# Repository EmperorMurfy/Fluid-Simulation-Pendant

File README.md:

# Fluid Simulation Pendant
A Fluid Simulation Pendant Inspired by Mitxela

<table>
  <tr>
    <td></td>
    <td></td>
  </tr>
</table>

## Overview
Since January, I've been particularly inspired by Mitxela's Fluid Simulation Pendant.
A watch-sized device, it contains it's own charlieplexed LED display driven by an STM32.
This allows the device to run a particle simulation that responds to gravity in real time.
In other words, water is displayed on it's LED display that flows and settles naturally as you move.
 
As a beginner, I was thoroughly intrigued. This came at the perfect opportunity as I sought to enter electronic design.
So, with no former experience, I set out to build my own from scratch.

You can find my full devlog at [Blueprint](https://blueprint.hackclub.com/projects/14158)
--

## PCB
This project was designed in KiCAD. V1 utilized a lilypad design with two 2-layer daughter boards (see devlog).
V2 features a singular 4-layer board, merging V1's two daughter boards. It tackles significant issues from V1.

### Schematic

### PCB
<table>
  <tr>
    <td></td>
    <td></td>
  </tr>
</table>

## 3D View

<table>
  <tr>
    <td></td>
    <td></td>
  </tr>
</table>

## Setup

OBTAIN PCB
1) Download project files from Github. Use KiCAD to open hardware files.
2) Export & Upload to JLCPCB through Fabrication Toolkit
3) Select PCBA. Make sure you click on Standard + assemble on both sides. 
4) Follow on screen instructions. Verify BOM contents.

5) Purchase and await arrival.

While waiting, you can 3D print the case included in the CAD folder.
Download both "Case.3mf" and "Back Lid.3mf"
Alternatively, you can access the CAD on [Onshape](https://cad.onshape.com/documents/ce3587694f856aec528b28ab/w/4bfd7fa16d33233767ff6bdf/e/73e8d055661068f7b677968e?renderMode=0&uiState=69cc9a998e56fd57fc1aa12d)

ASSEMBLY 
1) Solder PH1 pins on the back of the PCB at drilled holes labeled BOOT0, NRST, DEBUG_TMS, GND, DEBUG_TCK, 3.3V
2) Connect to Nucleo's ST-LINK, Connect to PCB
3) Install STM32CubeProgrammer and STM32CubeIDE
4) Open software folder from downloaded project files, select STM32.ioc (this should open STM32CubeProgrammer)
5) Select generate code (this should open STM32CubeIDE)
6) Replace the generated main.cp or cpp with main.cp from project files, click run to save
8) Install PCB to case - Be CAREFUL! Putting it at an angle with the USB-C pointed towards the opening helps.
9) Plug the battery into PCB's JST-2 port
10) Install the back lid + push in the watch glass

## BOM
In order to program this device, you will need F to F Jumper Wire and a Nucleo (I used Nucleo-F446RE). 
I didn't include these items as you may already have them. Disclaimer: The cost and quantity of PCB components were determined by JLCPCB.
JLCPCB sources their components from LCSC, but price may be inaccurate. Likewise, JLCPCB charged more components than required (e.g I only need 1040 Green 0402 LEDs, not 1045)
Likewise, you'll need to order 5 PCBs & 2 PCBA minimum. I ordered 5 PCBs + associated PCBA. 

|Item                         |Qty |Cost  |URL                                                                                                                                                                                                                                                 |Reference                                                                                                                                                                                                                                                                                                                                                                                                                                                                                                                                                                                                                                                                                                                                                                                                                                                                                                                                                                                       |Mfg Part #            |
|-----------------------------|----|------|----------------------------------------------------------------------------------------------------------------------------------------------------------------------------------------------------------------------------------------------------|------------------------------------------------------------------------------------------------------------------------------------------------------------------------------------------------------------------------------------------------------------------------------------------------------------------------------------------------------------------------------------------------------------------------------------------------------------------------------------------------------------------------------------------------------------------------------------------------------------------------------------------------------------------------------------------------------------------------------------------------------------------------------------------------------------------------------------------------------------------------------------------------------------------------------------------------------------------------------------------------|----------------------|
|PCB                          |5   |$14.90|https://jlcpcb.com/                                                                                                                                                                                                                                 |-                                                                                                                                                                                                                                                                                                                                                                                                                                                                                                                                                                                                                                                                                                                                                                                                                                                                                                                                                                                               |-                     |
|4.7uF-0402                   |20  |$0.11 |https://www.lcsc.com/product-detail/C23733.html                                                                                                                                                                                                     |C1,C8                                                                                                                                                                                                                                                                                                                                                                                                                                                                                                                                                                                                                                                                                                                                                                                                                                                                                                                                                                                           |CL05A475MP5NRNC       |
|100nF-0402                   |40  |$0.05 |https://www.lcsc.com/product-detail/C1525.html?s_z=n_CL05B104KO5NNNC&spm=wm.ssy.bg.0.xh&lcsc_vid=EwBZBVRfFVVaVFdSR1hcUFBTQFUMUl1eEVFaVldeEQIxVlNRQlFeUVBfQFJcVzsOAxUeFF5JWBYZEEoKFBINSQcJGk4eFQsCAgIaSgADAwAHC0slRVJZVFdIHxUDCw%3D%3D               |C2,C3,C4,C5,C6,C7                                                                                                                                                                                                                                                                                                                                                                                                                                                                                                                                                                                                                                                                                                                                                                                                                                                                                                                                                                               |CL05B104KO5NNNC       |
|1uF                          |30  |$0.12 |https://www.lcsc.com/product-detail/C52923.html?s_z=n_CL05A105KA5NQNC&spm=wm.ssy.bg.0.xh&lcsc_vid=EwBZBVRfFVVaVFdSR1hcUFBTQFUMUl1eEVFaVldeEQIxVlNRQlFeUVFTQ1heXzsOAxUeFF5JWBYZEEoKFBINSQcJGk4eFQsCAgIaSgADAwAHC0slRlRcUkoOAwwC                      |C9,C10                                                                                                                                                                                                                                                                                                                                                                                                                                                                                                                                                                                                                                                                                                                                                                                                                                                                                                                                                                                          |CL05A105KA5NQNC       |
|1uF-0402                     |-   |-     |https://www.lcsc.com/product-detail/C52923.html?s_z=n_CL05A105KA5NQNC&spm=wm.ssy.bg.0.xh&lcsc_vid=EwBZBVRfFVVaVFdSR1hcUFBTQFUMUl1eEVFaVldeEQIxVlNRQlFeUVFTQ1heXzsOAxUeFF5JWBYZEEoKFBINSQcJGk4eFQsCAgIaSgADAwAHC0slRlRcUkoOAwwC                      |C11,C12                                                                                                                                                                                                                                                                                                                                                                                                                                                                                                                                                                                                                                                                                                                                                                                                                                                                                                                                                                                         |CL05A105KA5NQNC       |
|Green 0402 LED               |1045|$29.88|https://www.lcsc.com/product-detail/C74338.html?s_z=n_16-213%252FGHC-YR1S1%252F3T&spm=wm.ssy.bg.0.xh&lcsc_vid=EwBZBVRfFVVaVFdSR1hcUFBTQFUMUl1eEVFaVldeEQIxVlNRQlFeUVNQQlJfVDsOAxUeFF5JWBYZEEoKFBINSQcJGk4eFQsCAgIaSgADAwAHC0slRVdaU1RRWQkaCgg%3D    |D6,D7,D8,D9,D10,D11,D20,D21,D22,D23,D24,D25,D26,D27,D28,D29,D35,D36,D37,D38,D39,D40,D41,D42,D43,D44,D45,D46,D50,D51,D52,D53,D54,D55,D56,D57,D58,D59,D60,D61,D62,D63,D66,D67,D68,D69,D70,D71,D72,D73,D74,D75,D76,D77,D78,D79,D81,D82,D83,D84,D85,D86,D87,D88,D89,D90,D91,D92,D93,D94,D95,D96,D97,D98,D99,D100,D101,D102,D103,D104,D105,D106,D107,D108,D109,D110,D111,D112,D113,D114,D115,D116,D117,D118,D119,D120,D121,D122,D123,D124,D125,D126,D127,D128,D129,D130,D131,D132,D133,D134,D135,D136,D137,D138,D139,D140,D141,D142,D143,D144,D145,D146,D147,D148,D149,D150,D151,D152,D153,D154,D155,D156,D157,D158,D159,D160,D161,D162,D163,D164,D165,D166,D167,D168,D169,D170,D171,D172,D173,D174,D175,D176,D178,D179,D180,D181,D182,D183,D184,D185,D186,D187,D188,D189,D190,D191,D194,D195,D196,D197,D198,D199,D200,D201,D202,D203,D204,D205,D206,D207,D211,D212,D213,D214,D215,D216,D217,D218,D219,D220,D221,D222,D228,D229,D230,D231,D232,D233,D234,D235,D236,D237,D246,D247,D248,D249,D250,D251|16-213/GHC-YR1S1/3T   |
|Red 0402 LED                 |5   |$0.35 |https://www.lcsc.com/product-detail/C264407.html?s_z=n_16-213%252FR6C-AQ2R2B%252F3T&spm=wm.ssy.bg.0.xh&lcsc_vid=EwBZBVRfFVVaVFdSR1hcUFBTQFUMUl1eEVFaVldeEQIxVlNRQlFeUVFRR1RZUzsOAxUeFF5JWBYZEEoKFBINSQcJGk4eFQsCAgIaSgADAwAHC0slQlNXVVdIHxUDCw%3D%3D|D257                                                                                                                                                                                                                                                                                                                                                                                                                                                                                                                                                                                                                                                                                                                                                                                                                                                                                                                                                                                            |16-213/R6C-AQ2R2B/3T  |
|Conn_01x01_Pin               |125 |-     |-                                                                                                                                                                                                                                                   |J2,J3,J4,J5,J6,J7,J8,J9,J10,J11,J12,J13,J14,J15,J16,J17,J18,J19,J20,J21,J22,J23,J24,J25,J26                                                                                                                                                                                                                                                                                                                                                                                                                                                                                                                                                                                                                                                                                                                                                                                                                                                                                                     |DNP                   |
|Conn_01x02_Socket            |5   |$2.19 |https://www.lcsc.com/product-detail/C160352.html?s_z=n_C160352                                                                                                                                                                                      |J44                                                                                                                                                                                                                                                                                                                                                                                                                                                                                                                                                                                                                                                                                                                                                                                                                                                                                                                                                                                             |B2B-PH-SM4-TB(LF)(SN) |
|22                           |95  |$0.08 |https://www.lcsc.com/product-detail/C25092.html?s_z=n_0402WGF220JTCE&spm=wm.ssy.bg.0.xh&lcsc_vid=EwBZBVRfFVVaVFdSR1hcUFBTQFUMUl1eEVFaVldeEQIxVlNRQlFeUVxUTlhbUzsOAxUeFF5JWBYZEEoKFBINSQcJGk4eFQsCAgIaSgADAwAHC0slRldeVFFUWQkaCgg%3D                 |R1,R2,R3,R4,R5,R6,R7,R8,R9,R10,R11,R12,R13,R14,R15,R16,R17                                                                                                                                                                                                                                                                                                                                                                                                                                                                                                                                                                                                                                                                                                                                                                                                                                                                                                                                      |0402WGF220JTCE        |
|20K                          |20  |$0.02 |https://www.lcsc.com/product-detail/C25765.html?s_z=n_0402WGF2002TCE&spm=wm.ssy.bg.0.xh&lcsc_vid=EwBZBVRfFVVaVFdSR1hcUFBTQFUMUl1eEVFaVldeEQIxVlNRQlFeUVxSRlRXVTsOAxUeFF5JWBYZEEoKFBINSQcJGk4eFQsCAgIaSgADAwAHC0slRVReXlZIHxUDCw%3D%3D               |R18                                                                                                                                                                                                                                                                                                                                                                                                                                                                                                                                                                                                                                                                                                                                                                                                                                                                                                                                                                                             |0402WGF2002TCE        |
|1k                           |20  |$0.01 |https://www.lcsc.com/product-detail/C11702.html?s_z=n_0402WGF1001TC&spm=wm.ssy.bg.0.xh&lcsc_vid=Q1MNU1YDQwJcBgIAEldWVQcERldfAVZWEQRaBlNWQVQxVlNRQlFfVVZTR1RcXjsOAxUeFF5JWBYZEEoKFBINSQcJGk4eFQsCAgIaSgADAwAHC0slRVRZUVFIHxUDCw%3D%3D                |R19                                                                                                                                                                                                                                                                                                                                                                                                                                                                                                                                                                                                                                                                                                                                                                                                                                                                                                                                                                                             |0402WGF1001TC         |
|10k                          |25  |$0.03 |https://www.lcsc.com/product-detail/C25744.html?s_z=n_0402WGF1002TCE&spm=wm.ssy.bg.0.xh&lcsc_vid=EwBZBVRfFVVaVFdSR1hcUFBTQFUMUl1eEVFaVldeEQIxVlNRQlFeUVxQQ1BdUDsOAxUeFF5JWBYZEEoKFBINSQcJGk4eFQsCAgIaSgADAwAHC0slRlBZV1ZIHxUDCw%3D%3D               |R20, R21,R22                                                                                                                                                                                                                                                                                                                                                                                                                                                                                                                                                                                                                                                                                                                                                                                                                                                                                                                                                                                    |0402WGF1002TCE        |
|5.1K                         |20  |$0.02 |https://www.lcsc.com/product-detail/C25905.html?s_z=n_0402WGF5101TCE&spm=wm.ssy.bg.0.xh&lcsc_vid=EwBZBVRfFVVaVFdSR1hcUFBTQFUMUl1eEVFaVldeEQIxVlNRQlFeUVxRR1dXUjsOAxUeFF5JWBYZEEoKFBINSQcJGk4eFQsCAgIaSgADAwAHC0slRVRZU1BIHxUDCw%3D%3D               |R23,R24                                                                                                                                                                                                                                                                                                                                                                                                                                                                                                                                                                                                                                                                                                                                                                                                                                                                                                                                                                                         |0402WGF5101TCE        |
|TestPoint                    |15  |      |-                                                                                                                                                                                                                                                   |TP1,TP2,TP3                                                                                                                                                                                                                                                                                                                                                                                                                                                                                                                                                                                                                                                                                                                                                                                                                                                                                                                                                                                     |DNP                   |
|STM32U575RGTx                |5   |$27.84|                                                                                                                                                                                                                                                    |U1                                                                                                                                                                                                                                                                                                                                                                                                                                                                                                                                                                                                                                                                                                                                                                                                                                                                                                                                                                                              |STM32U575RGT6         |
|ADXL363                      |5   |$90.77|https://www.lcsc.com/product-detail/C579464.html?s_z=n_ADXL363&spm=wm.ssy.bg.2.xh&lcsc_vid=EwBZBVRfFVVaVFdSR1hcUFBTQFUMUl1eEVFaVldeEQIxVlNRQlFeUV1WT1ReVzsOAxUeFF5JWBYZEEoKFBINSQcJGk4eFQsCAgIaSgADAwAHC0slRVRXV1FIHxUDCw%3D%3D                     |U2                                                                                                                                                                                                                                                                                                                                                                                                                                                                                                                                                                                                                                                                                                                                                                                                                                                                                                                                                                                              |ADXL363BCCZ-RL7       |
|USBLC6-2P6                   |5   |$1.23 |https://www.lcsc.com/product-detail/C15999.html?s_z=n_USBLC6-2P6&spm=wm.ssy.bg.0.xh&lcsc_vid=EwBZBVRfFVVaVFdSR1hcUFBTQFUMUl1eEVFaVldeEQIxVlNRQlFeUV1SRVdZUzsOAxUeFF5JWBYZEEoKFBINSQcJGk4eFQsCAgIaSgADAwAHC0slQlZXU1JSWQkaCgg%3D                     |U3                                                                                                                                                                                                                                                                                                                                                                                                                                                                                                                                                                                                                                                                                                                                                                                                                                                                                                                                                                                              |USBLC6-2P6            |
|MCP73832-2-MC                |5   |$5.19 |https://www.lcsc.com/product-detail/C511264.html?s_z=n_MCP73832T-2ACI%252FMC&spm=wm.ssy.bg.0.xh&lcsc_vid=EwBZBVRfFVVaVFdSR1hcUFBTQFUMUl1eEVFaVldeEQIxVlNRQlFeUV1TTlVfVjsOAxUeFF5JWBYZEEoKFBINSQcJGk4eFQsCAgIaSgADAwAHC0slRlRXXl1IHxUDCw%3D%3D       |U4                                                                                                                                                                                                                                                                                                                                                                                                                                                                                                                                                                                                                                                                                                                                                                                                                                                                                                                                                                                              |MCP73832T-2ACI/MC     |
|TPS7A20xxxDQN                |5   |$1.59 |https://www.lcsc.com/product-detail/C46459900.html?s_z=n_TPS7A2033DQNR&spm=wm.ssy.bg.0.xh&lcsc_vid=EwBZBVRfFVVaVFdSR1hcUFBTQFUMUl1eEVFaVldeEQIxVlNRQlFeUV1QT1NbXjsOAxUeFF5JWBYZEEoKFBINSQcJGk4eFQsCAgIaSgADAwAHC0slQlBfVVJSWQkaCgg%3D               |U5                                                                                                                                                                                                                                                                                                                                                                                                                                                                                                                                                                                                                                                                                                                                                                                                                                                                                                                                                                                              |TPS7A2033DQNR         |
|TYPE-C_16P_QTWT              |5   |$0.45 |https://www.lcsc.com/product-detail/C5187472.html?s_z=n_TYPE-C%252016P%2520QTWT&spm=wm.ssy.bg.0.xh&lcsc_vid=EwBZBVRfFVVaVFdSR1hcUFBTQFUMUl1eEVFaVldeEQIxVlNRQlFeUV1RQVdfVjsOAxUeFF5JWBYZEEoKFBINSQcJGk4eFQsCAgIaSgADAwAHC0slQ1daUl1fR1FADxALGw%3D%3D|USB1                                                                                                                                                                                                                                                                                                                                                                                                                                                                                                                                                                                                                                                                                                                                                                                                                                                                                                                                                                                            |TYPE-C 16P QTWT       |
|Setup Fee                    |-   |$50.74|-                                                                                                                                                                                                                                                   |-                                                                                                                                                                                                                                                                                                                                                                                                                                                                                                                                                                                                                                                                                                                                                                                                                                                                                                                                                                                               |-                     |
|Stencil                      |-   |$16.30|-                                                                                                                                                                                                                                                   |-                                                                                                                                                                                                                                                                                                                                                                                                                                                                                                                                                                                                                                                                                                                                                                                                                                                                                                                                                                                               |-                     |
|Feeders Loading Fee          |-   |$25.84|-                                                                                                                                                                                                                                                   |-                                                                                                                                                                                                                                                                                                                                                                                                                                                                                                                                                                                                                                                                                                                                                                                                                                                                                                                                                                                               |-                     |
|SMT Assembly                 |-   |$5.23 |-                                                                                                                                                                                                                                                   |-                                                                                                                                                                                                                                                                                                                                                                                                                                                                                                                                                                                                                                                                                                                                                                                                                                                                                                                                                                                               |-                     |
|Packaging Fee                |    |$0.49 |-                                                                                                                                                                                                                                                   |-                                                                                                                                                                                                                                                                                                                                                                                                                                                                                                                                                                                                                                                                                                                                                                                                                                                                                                                                                                                               |-                     |
|JLCPCB Shipping              |-   |$50.04|-                                                                                                                                                                                                                                                   |-                                                                                                                                                                                                                                                                                                                                                                                                                                                                                                                                                                                                                                                                                                                                                                                                                                                                                                                                                                                               |-                     |
|JLCPCB Custom Duties & Taxes |-   |$86.68|-                                                                                                                                                                                                                                                   |-                                                                                                                                                                                                                                                                                                                                                                                                                                                                                                                                                                                                                                                                                                                                                                                                                                                                                                                                                                                               |-                     |
|Li-Polymer 402025 150mAh 3.7V|5   |$29.75|https://www.digikey.com/en/products/detail/adafruit-industries-llc/1317/5054547                                                                                                                                                                     |-                                                                                                                                                                                                                                                                                                                                                                                                                                                                                                                                                                                                                                                                                                                                                                                                                                                                                                                                                                                               |-                     |
|PH1-01-UA                    |40  |$1.16 |https://www.digikey.com/en/products/detail/adam-tech/PH1-01-UA/9830231                                                                                                                                                                              |-                                                                                                                                                                                                                                                                                                                                                                                                                                                                                                                                                                                                                                                                                                                                                                                                                                                                                                                                                                                               |-                     |
|Digikey Shipping             |-   |$6.99 |-                                                                                                                                                                                                                                                   |-                                                                                                                                                                                                                                                                                                                                                                                                                                                                                                                                                                                                                                                                                                                                                                                                                                                                                                                                                                                               |-                     |
|Watch Glass 43mm Dia         |1   |$7.69 |https://www.amazon.com/dp/B09QXCGNG6?ref_=ppx_hzsearch_conn_dt_b_fed_asin_title_1                                                                                                                                                                   |                                                                                                                                                                                                                                                                                                                                                                                                                                                                                                                                                                                                                                                                                                                                                                                                                                                                                                                                                                                                |                      |
|Total                        |-   |$456  |                                                                                                                                                                                                                                                    |                                                                                                                                                                                                                                                                                                                                                                                                                                                                                                                                                                                                                                                                                                                                                                                                                                                                                                                                                                                                |                      |

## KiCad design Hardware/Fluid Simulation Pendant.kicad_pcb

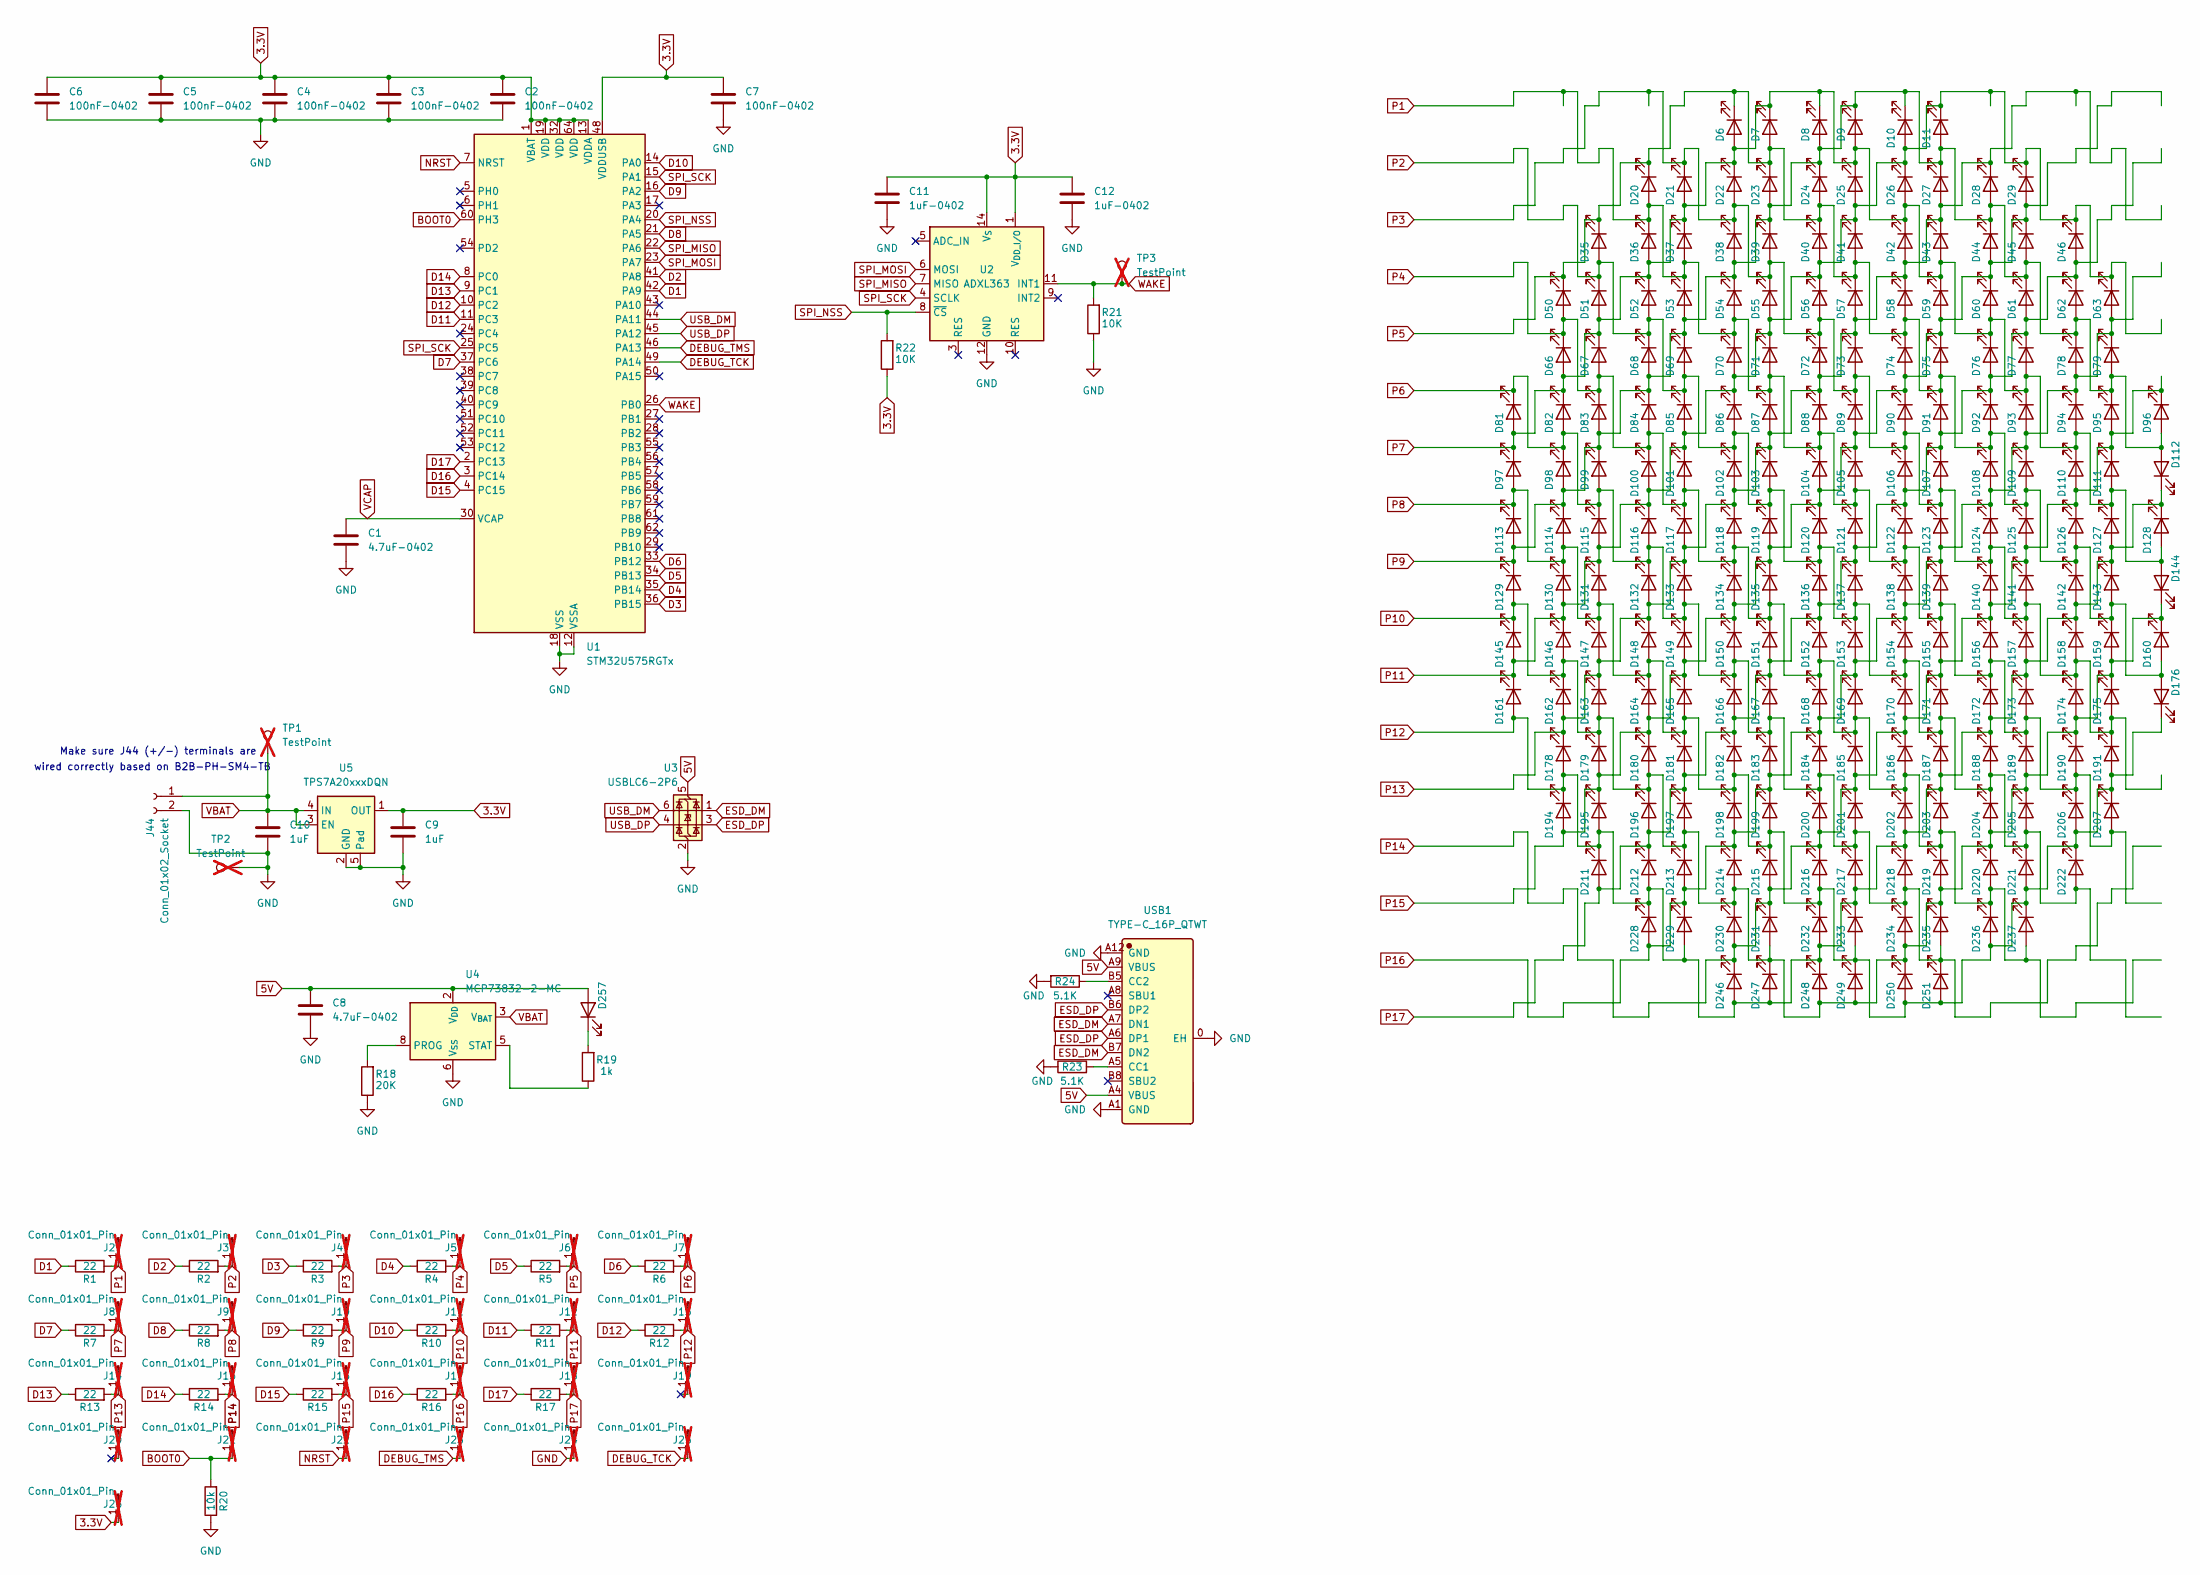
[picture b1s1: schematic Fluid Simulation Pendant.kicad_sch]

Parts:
C1, C8: 4.7uF-0402; C_0402_1005Metric; Mfg Part # CL05A475MP5NRNC
C2, C3, C4, C5, C6, C7: 100nF-0402; C_0402_1005Metric; Mfg Part # CL05B104KO5NNNC
C9, C10: 1uF; C_0402_1005Metric; Mfg Part # CL05A105KA5NQNC
C11, C12: 1uF-0402; C_0402_1005Metric; Mfg Part # CL05A105KA5NQNC
D6, D7, D8, D9, D10, D11, D20, D21, D22, D23, D24, D25, D26, D27, D28, D29, D35, D36, D37, D38, D39, D40, D41, D42, D43, D44, D45, D46, D50, D51, D52, D53, D54, D55, D56, D57, D58, D59, D60, D61, D62, D63, D66, D67, D68, D69, D70, D71, D72, D73, D74, D75, D76, D77, D78, D79, D81, D82, D83, D84, D85, D86, D87, D88, D89, D90, D91, D92, D93, D94, D95, D96, D97, D98, D99, D100, D101, D102, D103, D104, D105, D106, D107, D108, D109, D110, D111, D112, D113, D114, D115, D116, D117, D118, D119, D120, D121, D122, D123, D124, D125, D126, D127, D128, D129, D130, D131, D132, D133, D134, D135, D136, D137, D138, D139, D140, D141, D142, D143, D144, D145, D146, D147, D148, D149, D150, D151, D152, D153, D154, D155, D156, D157, D158, D159, D160, D161, D162, D163, D164, D165, D166, D167, D168, D169, D170, D171, D172, D173, D174, D175, D176, D178, D179, D180, D181, D182, D183, D184, D185, D186, D187, D188, D189, D190, D191, D194, D195, D196, D197, D198, D199, D200, D201, D202, D203, D204, D205, D206, D207, D211, D212, D213, D214, D215, D216, D217, D218, D219, D220, D221, D222, D228, D229, D230, D231, D232, D233, D234, D235, D236, D237, D246, D247, D248, D249, D250, D251: Green 0402 LED; LED_0402_1005Metric; Mfg Part # 16-213/GHC-YR1S1/3T
D257: Red 0402 LED; LED_0402_1005Metric; Mfg Part # 16-213/R6C-AQ2R2B/3T
J2, J3, J4, J5, J6, J7, J8, J9, J10, J11, J12, J13, J14, J15, J16, J17, J18, J19, J20, J21, J22, J23, J24, J25, J26: Conn_01x01_Pin; TestPoint_THTPad_D2.0mm_Drill1.0mm; not fitted
J44: Conn_01x02_Socket; JST_PH_B2B-PH-SM4-TB_1x02-1MP_P2.00mm_Vertical; Mfg Part # B2B-PH-SM4-TB(LF)(SN)
R1, R2, R3, R4, R5, R6, R7, R8, R9, R10, R11, R12, R13, R14, R15, R16, R17: 22; R_0402_1005Metric; Mfg Part # 0402WGF220JTCE
R18: 20K; R_0402_1005Metric; Mfg Part # 0402WGF2002TCE
R19: 1k; R_0402_1005Metric; Mfg Part # 0402WGF1001TC
R20: 10k; R_0402_1005Metric; Mfg Part # 0402WGF1002TCE
R21, R22: 10K; R_0402_1005Metric; Mfg Part # 0402WGF1002TCE
R23, R24: 5.1K; R_0402_1005Metric; Mfg Part # 0402WGF5101TCE
TP1, TP2, TP3: TestPoint; TestPoint_Pad_2.0x2.0mm; not fitted
U1: STM32U575RGTx; LQFP-64_10x10mm_P0.5mm; Mfg Part # STM32U575RGT6
U2: ADXL363; Analog_LGA-16_3.25x3mm_P0.5mm_LayoutBorder3x5y; Mfg Part # ADXL363BCCZ-RL7
U3: USBLC6-2P6; SOT-666; Mfg Part # USBLC6-2P6
U4: MCP73832-2-MC; DFN-8-1EP_3x2mm_P0.5mm_EP1.7x1.4mm; Mfg Part # MCP73832T-2ACI/MC
U5: TPS7A20xxxDQN; Texas_X2SON-4_1x1mm_P0.65mm; Mfg Part # TPS7A2033DQNR
USB1: TYPE-C_16P_QTWT; Manufacturer Part TYPE-C 16P QTWT; LCSC C5187472

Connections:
3.3V: C2.1, C3.1, C4.1, C5.1, C6.1, C7.1, C9.1, C11.1, C12.1, J26.1, R22.1, U1.1 (VBAT), U1.13 (VDDA), U1.19 (VDD), U1.32 (VDD), U1.48 (VDDUSB), U1.64 (VDD), U2.1 (V_{DD_I/O}), U2.14 (V_{S}), U5.1 (OUT)
5V: C8.1, D257.2 (A), U3.5 (VBUS), U4.1 (V_{DD}), U4.2 (V_{DD}), USB1.A4 (VBUS), USB1.A9 (VBUS)
BOOT0: J21.1, R20.2, U1.60 (PH3)
D1: R1.1, U1.42 (PA9)
D2: R2.1, U1.41 (PA8)
D3: R3.1, U1.36 (PB15)
D4: R4.1, U1.35 (PB14)
D5: R5.1, U1.34 (PB13)
D6: R6.1, U1.33 (PB12)
D7: R7.1, U1.37 (PC6)
D8: R8.1, U1.21 (PA5)
D9: R9.1, U1.16 (PA2)
D10: R10.1, U1.14 (PA0)
D11: R11.1, U1.11 (PC3)
D12: R12.1, U1.10 (PC2)
D13: R13.1, U1.9 (PC1)
D14: R14.1, U1.8 (PC0)
D15: R15.1, U1.4 (PC15)
D16: R16.1, U1.3 (PC14)
D17: R17.1, U1.2 (PC13)
DEBUG_TCK: J25.1, U1.49 (PA14)
DEBUG_TMS: J23.1, U1.46 (PA13)
ESD_DM: U3.1 (I/O1), USB1.A7 (DN1), USB1.B7 (DN2)
ESD_DP: U3.3 (I/O2), USB1.A6 (DP1), USB1.B6 (DP2)
GND: C1.2, C2.2, C3.2, C4.2, C5.2, C6.2, C7.2, C8.2, C9.2, C10.2, C11.2, C12.2, J24.1, J44.2, R18.1, R20.1, R21.1, R23.1, R24.2, TP2.1, U1.12 (VSSA), U1.18 (VSS), U1.31 (VSS), U1.47 (VSS), U1.63 (VSS), U2.12 (GND), U2.13 (GND), U2.16 (GND), U3.2 (GND), U4.6 (V_{SS}), U5.2 (GND), U5.5 (Pad), USB1.0 (EH), USB1.A1 (GND), USB1.A12 (GND)
NRST: J22.1, U1.7 (NRST)
unnamed: D257.1 (K), R19.2
unnamed: R18.2, U4.8 (PROG)
unnamed: R19.1, U4.5 (STAT)
unnamed: R23.2, USB1.A5 (CC1)
unnamed: R24.1, USB1.B5 (CC2)
P1: D20.2 (A), D36.1 (K), D37.2 (A), D53.1 (K), D54.2 (A), D70.1 (K), D71.2 (A), D87.1 (K), D88.2 (A), D104.1 (K), D105.2 (A), D121.1 (K), D122.2 (A), D138.1 (K), D139.2 (A), D155.1 (K), D156.2 (A), D172.1 (K), D173.2 (A), D189.1 (K), D190.2 (A), D206.1 (K), D207.2 (A), J2.1, R1.2
P2: D35.2 (A), D51.1 (K), D52.2 (A), D68.1 (K), D69.2 (A), D85.1 (K), D86.2 (A), D102.1 (K), D103.2 (A), D119.1 (K), D120.2 (A), D136.1 (K), D137.2 (A), D153.1 (K), D154.2 (A), D170.1 (K), D171.2 (A), D187.1 (K), D188.2 (A), D204.1 (K), D205.2 (A), D221.1 (K), D222.2 (A), J3.1, R2.2
P3: D21.1 (K), D22.2 (A), D38.1 (K), D39.2 (A), D55.1 (K), D56.2 (A), D72.1 (K), D73.2 (A), D89.1 (K), D90.2 (A), D106.1 (K), D107.2 (A), D123.1 (K), D124.2 (A), D140.1 (K), D141.2 (A), D157.1 (K), D158.2 (A), D174.1 (K), D175.2 (A), D191.1 (K), J4.1, R3.2
P4: D50.2 (A), D66.1 (K), D67.2 (A), D83.1 (K), D84.2 (A), D100.1 (K), D101.2 (A), D117.1 (K), D118.2 (A), D134.1 (K), D135.2 (A), D151.1 (K), D152.2 (A), D168.1 (K), D169.2 (A), D185.1 (K), D186.2 (A), D202.1 (K), D203.2 (A), D219.1 (K), D220.2 (A), D236.1 (K), D237.2 (A), J5.1, R4.2
P5: D6.1 (K), D7.2 (A), D20.1 (K), D23.1 (K), D24.2 (A), D35.1 (K), D40.1 (K), D41.2 (A), D50.1 (K), D57.1 (K), D58.2 (A), D74.1 (K), D75.2 (A), D91.1 (K), D92.2 (A), D108.1 (K), D109.2 (A), D125.1 (K), D126.2 (A), D142.1 (K), D143.2 (A), D159.1 (K), D160.2 (A), D176.2 (A), J6.1, R5.2
P6: D81.1 (K), D82.2 (A), D98.1 (K), D99.2 (A), D115.1 (K), D116.2 (A), D132.1 (K), D133.2 (A), D149.1 (K), D150.2 (A), D166.1 (K), D167.2 (A), D183.1 (K), D184.2 (A), D200.1 (K), D201.2 (A), D217.1 (K), D218.2 (A), D234.1 (K), D235.2 (A), D251.1 (K), J7.1, R6.2
P7: D6.2 (A), D7.1 (K), D8.1 (K), D9.2 (A), D21.2 (A), D22.1 (K), D25.1 (K), D26.2 (A), D36.2 (A), D37.1 (K), D42.1 (K), D43.2 (A), D51.2 (A), D52.1 (K), D59.1 (K), D60.2 (A), D66.2 (A), D67.1 (K), D76.1 (K), D77.2 (A), D81.2 (A), D82.1 (K), D93.1 (K), D94.2 (A), D97.1 (K), D110.1 (K), D111.2 (A), D127.1 (K), D128.2 (A), D144.2 (A), J8.1, R7.2
P8: D97.2 (A), D113.1 (K), D114.2 (A), D130.1 (K), D131.2 (A), D147.1 (K), D148.2 (A), D164.1 (K), D165.2 (A), D176.1 (K), D181.1 (K), D182.2 (A), D191.2 (A), D198.1 (K), D199.2 (A), D206.2 (A), D207.1 (K), D215.1 (K), D216.2 (A), D221.2 (A), D222.1 (K), D232.1 (K), D233.2 (A), D236.2 (A), D237.1 (K), D249.1 (K), D250.2 (A), D251.2 (A), J9.1, R8.2
P9: D8.2 (A), D9.1 (K), D10.1 (K), D11.2 (A), D23.2 (A), D24.1 (K), D27.1 (K), D28.2 (A), D38.2 (A), D39.1 (K), D44.1 (K), D45.2 (A), D53.2 (A), D54.1 (K), D61.1 (K), D62.2 (A), D68.2 (A), D69.1 (K), D78.1 (K), D79.2 (A), D83.2 (A), D84.1 (K), D95.1 (K), D96.2 (A), D98.2 (A), D99.1 (K), D112.2 (A), D113.2 (A), D114.1 (K), D129.1 (K), J10.1, R9.2
P10: D129.2 (A), D144.1 (K), D145.1 (K), D146.2 (A), D159.2 (A), D160.1 (K), D162.1 (K), D163.2 (A), D174.2 (A), D175.1 (K), D179.1 (K), D180.2 (A), D189.2 (A), D190.1 (K), D196.1 (K), D197.2 (A), D204.2 (A), D205.1 (K), D213.1 (K), D214.2 (A), D219.2 (A), D220.1 (K), D230.1 (K), D231.2 (A), D234.2 (A), D235.1 (K), D247.1 (K), D248.2 (A), D249.2 (A), D250.1 (K), J11.1, R10.2
P11: D10.2 (A), D11.1 (K), D25.2 (A), D26.1 (K), D29.1 (K), D40.2 (A), D41.1 (K), D46.1 (K), D55.2 (A), D56.1 (K), D63.1 (K), D70.2 (A), D71.1 (K), D85.2 (A), D86.1 (K), D100.2 (A), D101.1 (K), D115.2 (A), D116.1 (K), D130.2 (A), D131.1 (K), D145.2 (A), D146.1 (K), D161.1 (K), J12.1, R11.2
P12: D112.1 (K), D127.2 (A), D128.1 (K), D142.2 (A), D143.1 (K), D157.2 (A), D158.1 (K), D161.2 (A), D172.2 (A), D173.1 (K), D178.2 (A), D187.2 (A), D188.1 (K), D194.1 (K), D195.2 (A), D202.2 (A), D203.1 (K), D211.1 (K), D212.2 (A), D217.2 (A), D218.1 (K), D228.1 (K), D229.2 (A), D232.2 (A), D233.1 (K), D246.2 (A), D247.2 (A), D248.1 (K), J13.1, R12.2
P13: D27.2 (A), D28.1 (K), D42.2 (A), D43.1 (K), D57.2 (A), D58.1 (K), D72.2 (A), D73.1 (K), D87.2 (A), D88.1 (K), D102.2 (A), D103.1 (K), D117.2 (A), D118.1 (K), D132.2 (A), D133.1 (K), D147.2 (A), D148.1 (K), D162.2 (A), D163.1 (K), D178.1 (K), J14.1, R13.2
P14: D95.2 (A), D96.1 (K), D110.2 (A), D111.1 (K), D125.2 (A), D126.1 (K), D140.2 (A), D141.1 (K), D155.2 (A), D156.1 (K), D170.2 (A), D171.1 (K), D185.2 (A), D186.1 (K), D200.2 (A), D201.1 (K), D215.2 (A), D216.1 (K), D230.2 (A), D231.1 (K), D246.1 (K), J15.1, R14.2
P15: D29.2 (A), D44.2 (A), D45.1 (K), D59.2 (A), D60.1 (K), D74.2 (A), D75.1 (K), D89.2 (A), D90.1 (K), D104.2 (A), D105.1 (K), D119.2 (A), D120.1 (K), D134.2 (A), D135.1 (K), D149.2 (A), D150.1 (K), D164.2 (A), D165.1 (K), D179.2 (A), D180.1 (K), D194.2 (A), D195.1 (K), J16.1, R15.2
P16: D63.2 (A), D78.2 (A), D79.1 (K), D93.2 (A), D94.1 (K), D108.2 (A), D109.1 (K), D123.2 (A), D124.1 (K), D138.2 (A), D139.1 (K), D153.2 (A), D154.1 (K), D168.2 (A), D169.1 (K), D183.2 (A), D184.1 (K), D198.2 (A), D199.1 (K), D213.2 (A), D214.1 (K), D228.2 (A), D229.1 (K), J17.1, R16.2
P17: D46.2 (A), D61.2 (A), D62.1 (K), D76.2 (A), D77.1 (K), D91.2 (A), D92.1 (K), D106.2 (A), D107.1 (K), D121.2 (A), D122.1 (K), D136.2 (A), D137.1 (K), D151.2 (A), D152.1 (K), D166.2 (A), D167.1 (K), D181.2 (A), D182.1 (K), D196.2 (A), D197.1 (K), D211.2 (A), D212.1 (K), J18.1, R17.2
SPI_MISO: U1.22 (PA6), U2.7 (MISO)
SPI_MOSI: U1.23 (PA7), U2.6 (MOSI)
SPI_NSS: R22.2, U1.20 (PA4), U2.8 (~CS)
SPI_SCK: U1.15 (PA1), U1.25 (PC5), U2.4 (SCLK)
USB_DM: U1.44 (PA11), U3.6 (I/O1)
USB_DP: U1.45 (PA12), U3.4 (I/O2)
VBAT: C10.1, J44.1, TP1.1, U4.3 (V_{BAT}), U4.4 (V_{BAT}), U5.3 (EN), U5.4 (IN)
VCAP: C1.1, U1.30 (VCAP)
WAKE: R21.2, TP3.1, U1.26 (PB0), U2.11 (INT1)

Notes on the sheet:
Make sure J44 (+/-) terminals are
wired correctly based on B2B-PH-SM4-TB

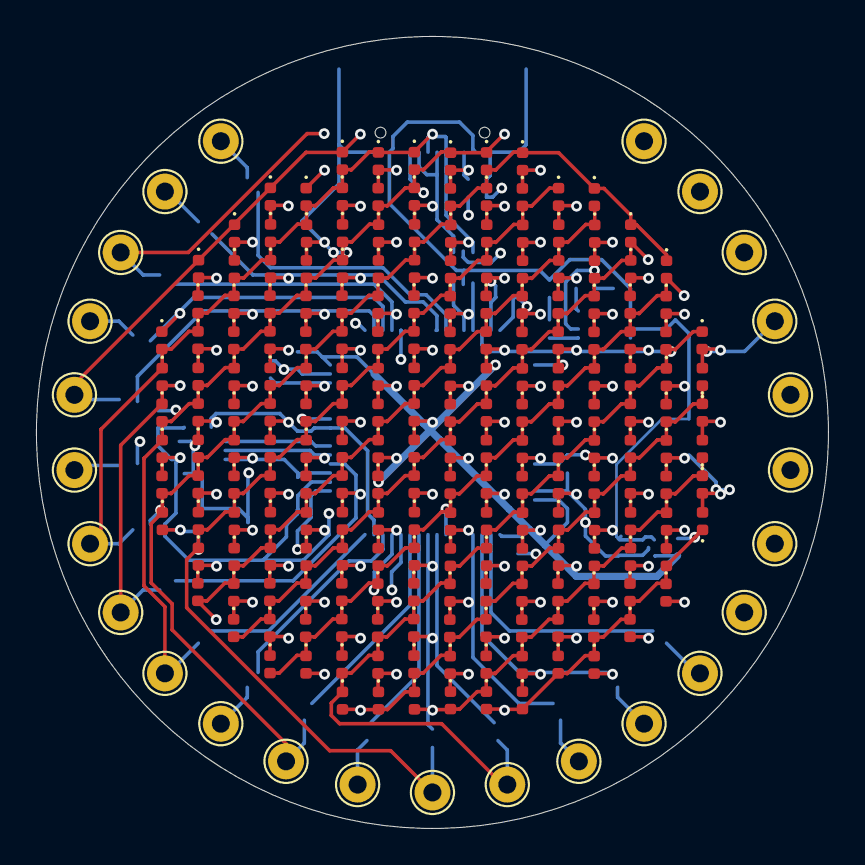
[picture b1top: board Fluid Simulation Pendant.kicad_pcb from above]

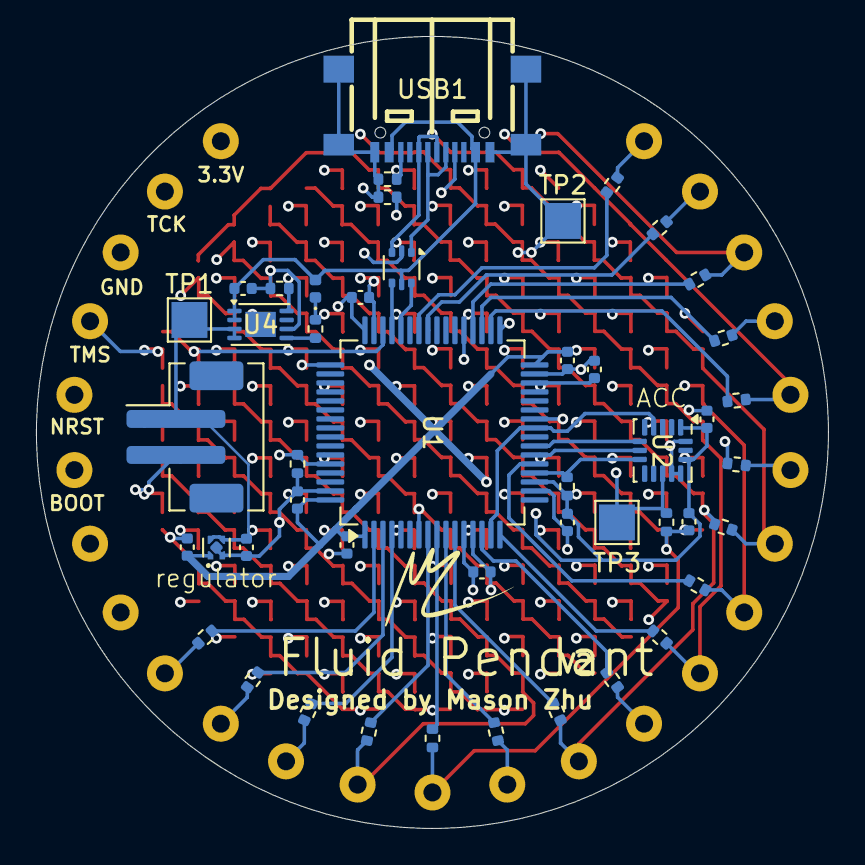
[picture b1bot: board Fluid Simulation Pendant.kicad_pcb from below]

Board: 4 copper layers, 44.0 x 44.0 mm, 280 parts (47 on the bottom side), 57 nets.

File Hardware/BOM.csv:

"Reference","Mfg Part #","LCSC","Link","Qty","Value","DNP","Exclude from BOM","Exclude from Board","Footprint","Datasheet","Manufacturer"
"C1,C8","CL05A475MP5NRNC","","","2","4.7uF-0402","","","","Capacitor_SMD:C_0402_1005Metric","~","Murata Electronics"
"C2,C3,C4,C5,C6,C7","CL05B104KO5NNNC","","","6","100nF-0402","","","","Capacitor_SMD:C_0402_1005Metric","~","Murata Electronics"
"C9,C10","CL05A105KA5NQNC","","","2","1uF","","","","Capacitor_SMD:C_0402_1005Metric","~","Murata Electronics"
"C11,C12","CL05A105KA5NQNC","","","2","1uF-0402","","","","Capacitor_SMD:C_0402_1005Metric","~","Murata Electronics"
"D6,D7,D8,D9,D10,D11,D20,D21,D22,D23,D24,D25,D26,D27,D28,D29,D35,D36,D37,D38,D39,D40,D41,D42,D43,D44,D45,D46,D50,D51,D52,D53,D54,D55,D56,D57,D58,D59,D60,D61,D62,D63,D66,D67,D68,D69,D70,D71,D72,D73,D74,D75,D76,D77,D78,D79,D81,D82,D83,D84,D85,D86,D87,D88,D89,D90,D91,D92,D93,D94,D95,D96,D97,D98,D99,D100,D101,D102,D103,D104,D105,D106,D107,D108,D109,D110,D111,D112,D113,D114,D115,D116,D117,D118,D119,D120,D121,D122,D123,D124,D125,D126,D127,D128,D129,D130,D131,D132,D133,D134,D135,D136,D137,D138,D139,D140,D141,D142,D143,D144,D145,D146,D147,D148,D149,D150,D151,D152,D153,D154,D155,D156,D157,D158,D159,D160,D161,D162,D163,D164,D165,D166,D167,D168,D169,D170,D171,D172,D173,D174,D175,D176,D178,D179,D180,D181,D182,D183,D184,D185,D186,D187,D188,D189,D190,D191,D194,D195,D196,D197,D198,D199,D200,D201,D202,D203,D204,D205,D206,D207,D211,D212,D213,D214,D215,D216,D217,D218,D219,D220,D221,D222,D228,D229,D230,D231,D232,D233,D234,D235,D236,D237,D246,D247,D248,D249,D250,D251,D257","16-213/R6C-AQ2R2B/3T","","","209","LED","","","","LED_SMD:LED_0402_1005Metric","~","Everlight Electronics Co Ltd"
"J2,J3,J4,J5,J6,J7,J8,J9,J10,J11,J12,J13,J14,J15,J16,J17,J18,J19,J20,J21,J22,J23,J24,J25,J26","","","","25","Conn_01x01_Pin","DNP","","","TestPoint:TestPoint_THTPad_D2.0mm_Drill1.0mm","~",""
"J44","JST B2B-PH-SM4-TB(LF)(SN)","","","1","Conn_01x02_Socket","","","","Connector_JST:JST_PH_B2B-PH-SM4-TB_1x02-1MP_P2.00mm_Vertical","~",""
"R1,R2,R3,R4,R5,R6,R7,R8,R9,R10,R11,R12,R13,R14,R15,R16,R17","0402WGF220JTCE","","","17","22","","","","Resistor_SMD:R_0402_1005Metric","~","YAGEO"
"R18","0402WGF2002TCE","","","1","20K","","","","Resistor_SMD:R_0402_1005Metric","~",""
"R19","0402WGF2002TCE","","","1","1k","","","","Resistor_SMD:R_0402_1005Metric","~","YAGEO"
"R20","0402WGF1001TCE","","","1","10k","","","","Resistor_SMD:R_0402_1005Metric","~","YAGEO"
"R21,R22","0402WGF1002TCE","","","2","10K","","","","Resistor_SMD:R_0402_1005Metric","~",""
"R23,R24","0402WGF5101TCE","","","2","5.1K","","","","Resistor_SMD:R_0402_1005Metric","~",""
"TP1,TP2,TP3","","","","3","TestPoint","DNP","","","TestPoint:TestPoint_Pad_2.0x2.0mm","~",""
"U1","STM32U575RGT6","","","1","STM32U575RGTx","","","","Package_QFP:LQFP-64_10x10mm_P0.5mm","https://www.st.com/resource/en/datasheet/stm32u575rg.pdf","STMicroelectronics"
"U2","ADXL363BCCZ-RL7","","","1","ADXL363","","","","Sensor_Motion:Analog_LGA-16_3.25x3mm_P0.5mm_LayoutBorder3x5y","https://www.analog.com/media/en/technical-documentation/data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","Analog Devices Inc."
"U3","USBLC6-2P6","","","1","USBLC6-2P6","","","","Package_TO_SOT_SMD:SOT-666","https://www.st.com/resource/en/datasheet/usblc6-2.pdf","STMicroelectronics"
"U4","MCP73832T-2ACI/MC","","","1","MCP73832-2-MC","","","","Package_DFN_QFN:DFN-8-1EP_3x2mm_P0.5mm_EP1.7x1.4mm","http://ww1.microchip.com/downloads/en/DeviceDoc/20001984g.pdf","Microchip Tech"
"U5","TPS7A2033DQNR","","","1","TPS7A20xxxDQN","","","","Package_SON:Texas_X2SON-4_1x1mm_P0.65mm","https://www.ti.com/lit/ds/symlink/tps7a20.pdf","Texas Instruments"
"USB1","TYPE-C 16P QTWT","C5187472","","1","TYPE-C_16P_QTWT","","","","JLCImport:TYPE-C_16P_QTWT","https://wmsc.lcsc.com/wmsc/upload/file/pdf/v2/lcsc/220929173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","SHOU HAN"

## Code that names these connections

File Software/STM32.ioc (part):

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Mcu.Name=STM32U575RGTx
Mcu.Package=LQFP64
Mcu.UserName=STM32U575RGTx
PA0.Signal=GPIO_Output
PA1.Mode=Full_Duplex_Master
PA1.Signal=SPI1_SCK
PA11.Signal=USB_OTG_FS_DM
PA12.Signal=USB_OTG_FS_DP
PA13\ (JTMS/SWDIO).Signal=DEBUG_JTMS-SWDIO
PA14\ (JTCK/SWCLK).Signal=DEBUG_JTCK-SWCLK
PA2.Signal=GPIO_Output
PA4.Signal=GPIO_Output
PA5.Signal=GPIO_Output
PA6.Mode=Full_Duplex_Master
PA6.Signal=SPI1_MISO
PA7.Mode=Full_Duplex_Master
PA7.Signal=SPI1_MOSI
PA8.Signal=GPIO_Output
PA9.Signal=GPIO_Output
PB0.GPIOParameters=GPIO_ModeDefaultEXTI
PB0.GPIO_ModeDefaultEXTI=GPIO_MODE_IT_RISING
PB0.Signal=GPXTI0
PB12.Signal=GPIO_Output
PB13.Signal=GPIO_Output
PB14.Signal=GPIO_Output
PB15.Signal=GPIO_Output
PC0.Signal=GPIO_Output
PC1.Signal=GPIO_Output
PC13.Signal=GPIO_Output
PC14-OSC32_IN\ (PC14).Signal=GPIO_Output
PC15-OSC32_OUT\ (PC15).Signal=GPIO_Output
PC2.Signal=GPIO_Output
PC3.Signal=GPIO_Output
PC5.Signal=GPIO_Input
PC6.Signal=GPIO_Output
RCC.HSE_VALUE=16000000
board=custom

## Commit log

2026-04-01 Revise README title and enhance visuals
    Updated project title and added images to README.
2026-04-01 Update 3D printing instructions in README
    Clarified instructions for 3D printing the case and provided links to CAD files.
